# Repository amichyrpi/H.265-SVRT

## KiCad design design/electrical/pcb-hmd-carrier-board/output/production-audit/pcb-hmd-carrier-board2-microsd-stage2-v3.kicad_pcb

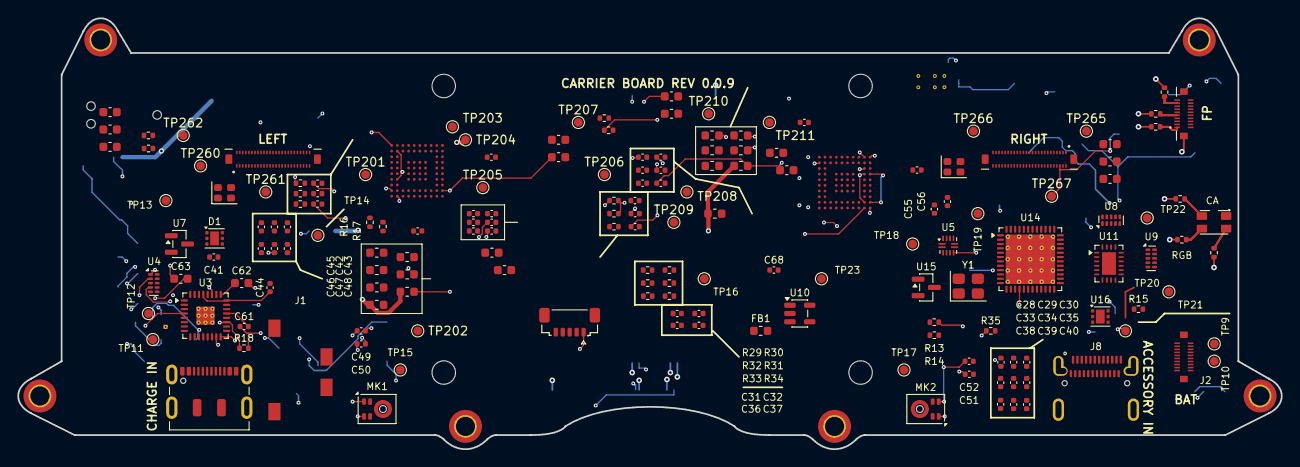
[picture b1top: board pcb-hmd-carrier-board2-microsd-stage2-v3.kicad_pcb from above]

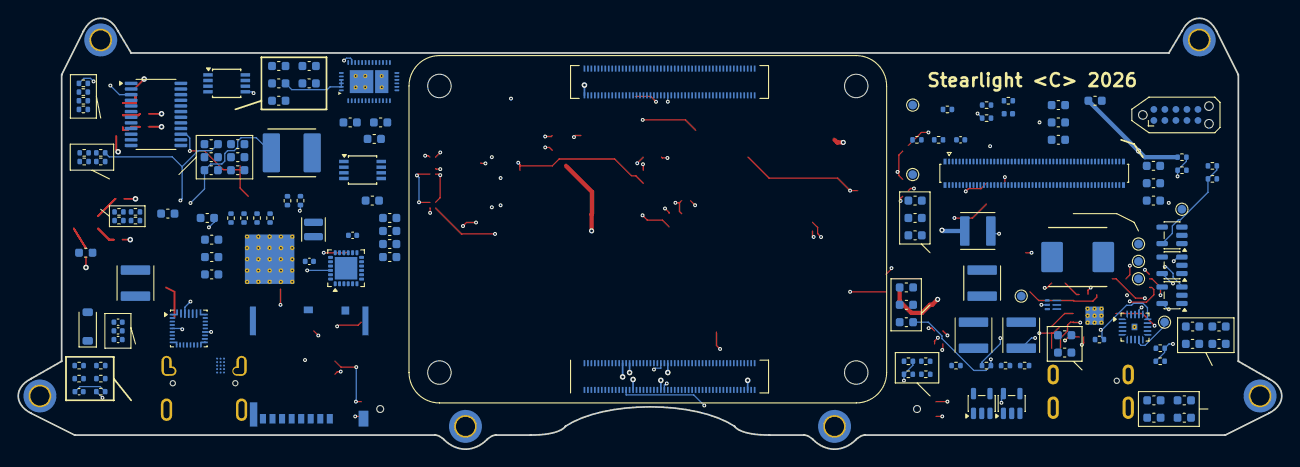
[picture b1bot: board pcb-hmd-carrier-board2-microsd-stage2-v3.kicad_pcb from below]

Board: 6 copper layers, 145.5 x 49.6 mm, 312 parts (138 on the bottom side), 10 nets.

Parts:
C1, C2, C3, C4, C5, C9, C10, C11, C13, C14, C19, C20, C21, C22, C23: 10u; C_0603_1608Metric
C6, C12, C15, C24, C25: 100n; C_0603_1608Metric
C7, C8: 330p; C_0603_1608Metric
C16: 4u7; C_0603_1608Metric
C17, C18: 47n; C_0603_1608Metric
C26, C20120, C20121, C20220, C20221: 1u; C_0603_1608Metric
C27: 47p; C_0603_1608Metric
C28, C29, C30, C31, C32, C33, C34, C35, C36, C37, C43, C48, C290, C291, C2010, C2011, C2012, C2013, C2014, C2015, C2016, C2017, C2020, C2021, C2022, C2023, C2024, C2025, C2026, C2027, C20130, C20131, C20132, C20230, C20231, C20232: 100n; C_0402_1005Metric
C38, C44, C45, C46, C47: 10u; C_0402_1005Metric
C39, C40, C41, C42: 1u; C_0402_1005Metric
C49, C50, C51, C52: 1u C0G; C_0402_1005Metric
C55, C56: 100n PCIe AC; C_0402_1005Metric
C57, C58: 100u low-ESR; C_0603_1608Metric
C59, C60: 22u 25V; C_0603_1608Metric
C61: 100n JACK MIC; C_0402_1005Metric
C62: 47u HP LEFT; C_0603_1608Metric
C63: 47u HP RIGHT; C_0603_1608Metric
C64: 4.7u 10V; C_0603_1608Metric
C65, C66: 10u 6.3V; C_0603_1608Metric
C67: 120p C0G; C_0402_1005Metric
C68: 100n USB3 RESET; C_0402_1005Metric
C260, C265: 2.2uF; C_0603_1608Metric
C261, C262, C266, C267: 1uF 10V; C_0603_1608Metric
C270, C272, C273, C2031, C2041, C2051, C2061: 4.7uF 10V; C_0603_1608Metric
C271: 2.2uF 10V; C_0603_1608Metric
C274: 1uF; C_0603_1608Metric
C280: 68n COMP; C_0402_1005Metric
C281: 10uF 10V; C_0402_1005Metric
C282, C283: 10uF 16V; C_0402_1005Metric
C301: 10uF SD POWER (CM4 LITE ONLY); C_0603_1608Metric
C2032, C2042, C2052, C2062: 10uF 6.3V; C_0603_1608Metric
C20122, C20123, C20222, C20223: 2.2u; C_0603_1608Metric
D1: TVS2200DRVR; WSON-6-1EP_2x2mm_P0.65mm_EP1x1.6mm
D11: TJ-S3227 RGB COMMON ANODE C601674; TOGIALED_TJ-S3227SW1TCGLCCYRGB-A5
D201: DFLS160-7; D_SOD-123
FB1: 600R@100MHz ferrite; L_0603_1608Metric
FB2011, FB2012, FB2013, FB2014, FB2015, FB2016, FB2017, FB2021, FB2022, FB2023, FB2024, FB2025, FB2026, FB2027: 600R@100MHz; L_0603_1608Metric
H1, H2, H3, H4, H5, H6: MountingHole_2.2mm_M2_DIN965_Pad_TopBottom
J1: SJ-43514-SMT-TR; SameSky_SJ-43514-SMT-TR
J2: BM28 BATTERY FLEX 5A + NTC/ID; Hirose_BM28B0.6-20DS_2-0.35V
J6: TAG-CONNECT SERVICE PADS (NO FIT); Tag-Connect_TC2050-IDC-NL_2x05_P1.27mm_Vertical
J7: DF40C-100DP-0.4V(51) TRACKING; Hirose_DF40C-100DP-0.4V_2x50-1MP_P0.4mm
J8: DX07S024JJ2R1300 ACCESSORY; JAE_DX07S024JJ2R1300
J9: DX07S016JA1R1500 CHARGE/SERVICE; USB_C_Receptacle_JAE_DX07S016JA1R1500
J10: PROX SENSOR - SM05B-SURS-TF; JST_SUR_SM05B-SURS-TF_1x05-1MP_P0.80mm_Horizontal
J11: BM28B0.6-20DS/2-0.35V BUTTON FLEX; Hirose_BM28B0.6-20DS_2-0.35V_BUTTONS
J201: J_DISPLAY_LEFT 245863050104829+; Kyocera_245863050104829_50P_P0.35
J202: J_DISPLAY_RIGHT 245863050104829+; Kyocera_245863050104829_50P_P0.35
J301: Molex 503398-1892 (CM4 LITE ONLY); SDCARD_MOLEX_503398-1892
L1: 0.47uH XFL4015-471MEC; L_0402_1005Metric
L2: SRP7050TA-2R2M 2.2uH 10A; Bourns_SRP7050TA
L3: SRP5030CA-1R0M 1uH 9A; Bourns_SRP5030CA
L203, L204, L205, L206: 2.2uH; L_Abracon_ASPI-4030S
L207: 4.7uH 1.6A DFE252010; L_APV_ANR252010
L208: 10uH >=2.5A WLED; L_Abracon_ASPI-4030S
MK1, MK2: IM73A135V01; Infineon_PG-LLGA-5-2
Module1: CM4 2GB/16GB/Wireless; Raspberry-Pi-4-Compute-Module
R1: 220k; R_0402_1005Metric
R2: 30k; R_0402_1005Metric
R3: 5.23k ILIM; R_0402_1005Metric
R4: 137k ILIM; R_0402_1005Metric
R5, R6, R290, R291, R292, R293: 2.2k I2C; R_0402_1005Metric
R7, R8, R294, R295, R2011, R2021: 10k; R_0402_1005Metric
R9: 30.1k TS; R_0402_1005Metric
R10: 10k NTC; R_0402_1005Metric
R11: 100R BATP; R_0402_1005Metric
R12: 6.04k 2S; R_0402_1005Metric
R13, R14: 200k; R_0402_1005Metric
R15: ILIM 1.5A TBD; R_0402_1005Metric
R16, R17: I2C 2.2k; R_0402_1005Metric
R18: MICBIAS 2.7k; R_0402_1005Metric
R19: 75k 1V05 FB; R_0402_1005Metric
R20: 100k 1V05 FB; R_0402_1005Metric
R21: 100k 1V05 PG; R_0402_1005Metric
R22: 10k WIFI EN; R_0402_1005Metric
R23: 10k BT EN; R_0402_1005Metric
R24: 75k MODE; R_0402_1005Metric
R25: 51k MODE; R_0402_1005Metric
R26: 10k CLKREQ; R_0402_1005Metric
R27: 2.2k CHG SCL; R_0402_1005Metric
R28: 2.2k CHG SDA; R_0402_1005Metric
R29: 10k OCI PU; R_0402_1005Metric
R30: 1.6k RREF VERIFY; R_0402_1005Metric
R31: 10k RESET PU; R_0402_1005Metric
R32: 10k SPI CLK PD; R_0402_1005Metric
R33: 10k SPI CS PD; R_0402_1005Metric
R34: 10k SPI MISO PU; R_0402_1005Metric
R35: 10k SPI MOSI PD; R_0402_1005Metric
R73, R76, R77, R78: 1k; R_0402_1005Metric
R74, R75: 330R; R_0402_1005Metric
R260, R265: 100k RESET pulldown; R_0402_1005Metric
R261, R266: 0R DNP to BL_PWM; R_0402_1005Metric
R280: 37.4k 1% ISET=33.2mA; R_0402_1005Metric
R281: 49.9k 1% 1.25MHz; R_0402_1005Metric
R282: 147k 1% OVP; R_0402_1005Metric
R283: 20k 1% OVP; R_0402_1005Metric
R284: 3k COMP; R_0402_1005Metric
R301: 12k 1% SD_PWR_ON PU (CM4 LITE ONLY); R_0402_1005Metric
R302, R303: 0R SD DETECT OPTION; R_0402_1005Metric
R2010, R2020: 2.00k 1%; R_0402_1005Metric
R2012: 10k ADDR 0x0F; R_0402_1005Metric
R2022: 10k ADDR 0x1F; R_0402_1005Metric
R2031: 453k 1%; R_0402_1005Metric
R2032, R2042, R2051, R2052, R2062: 100k 1%; R_0402_1005Metric
R2041: 200k 1%; R_0402_1005Metric
R2061: 91k 1%; R_0402_1005Metric
TP1, TP9, TP10, TP11, TP12, TP13, TP14, TP15, TP16, TP17, TP18, TP19, TP20, TP21, TP22, TP23: CHG_STAT; TestPoint_Pad_D1.0mm
TP2: PGOOD_5V; TestPoint_Pad_D1.0mm
TP3: BAT_ID; TestPoint_Pad_D1.0mm
TP4: +5V_SYS; TestPoint_Pad_D1.0mm
TP5: +3V3; TestPoint_Pad_D1.0mm
TP6: +1V05_USB; TestPoint_Pad_D1.0mm
TP7: GND; TestPoint_Pad_D1.0mm
TP8: VBAT_SYS; TestPoint_Pad_D1.0mm
TP201: DISPLAY_5V; TestPoint_Pad_D1.0mm
TP202: DISPLAY_3V3; TestPoint_Pad_D1.0mm
TP203: DISPLAY_1V8; TestPoint_Pad_D1.0mm
TP204: DISPLAY_1V2; TestPoint_Pad_D1.0mm
TP205: DISPLAY_1V15; TestPoint_Pad_D1.0mm
TP206: LCD_VSP +5V5; TestPoint_Pad_D1.0mm
TP207: LCD_VSN -5V5; TestPoint_Pad_D1.0mm
TP208: BL_EN; TestPoint_Pad_D1.0mm
TP209: BL_PWM GPIO12; TestPoint_Pad_D1.0mm
TP210: I2C_SDA_1V8; TestPoint_Pad_D1.0mm
TP211: I2C_SCL_1V8; TestPoint_Pad_D1.0mm
TP260: L S1_TEST NC; TestPoint_Pad_D1.0mm
TP261: L TE; TestPoint_Pad_D1.0mm
TP262: L LEDPWM; TestPoint_Pad_D1.0mm
TP265: R S1_TEST NC; TestPoint_Pad_D1.0mm
TP266: R TE; TestPoint_Pad_D1.0mm
TP267: R LEDPWM; TestPoint_Pad_D1.0mm
U1: TPS62825DMQR; Texas_DMQ0006A_VSON-HR-6_1.5x1.5mm
U2: TPS568230RJER; Texas_RJE0020A_VQFN-20-1EP_3x3mm_P0.45mm_EP0.675x0.76mm_The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
U3: TLV320AIC3204IRHBR; Texas_RHB0032M_VQFN-32-1EP_5x5mm_P0.5mm_EP2.1x2.1mm_Thermal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
U4: TPD4E05U06DQAR; USON-10_2.5x1.0mm_P0.5mm
U5: TUSB320LAIRWBR; Texas_X2QFN-12_1.6x1.6mm_P0.4mm
U6: BQ25798RQMR; Texas_RQM0029A_VQFN-29_4x4mm_P0.4mm
U7: TPD2EUSB30DRTR; SOT-23
U8, U9: TPD4EUSB30DQAR; USON-10_2.5x1.0mm_P0.5mm
U10: TLV75528PDBVR; SOT-23-5
U11: HD3SS3212IRKSR; Texas_RVC0020A_WQFN-20-1EP_3x4mm_P0.5mm_EP1.6x2.6mm
U12: TPS25751DREFR; Texas_REF0038A_WQFN-38_6x4mm_DualPad
U13: CAT24C512WI-GT3; TSSOP-8_3x3mm_P0.65mm
U14: UPD720202K8-711-BAA-A; QFN-48-1EP_7x7mm_P0.5mm_EP5.7x5.7mm_ThermalVias
U15: TLV803EA30DBZR; SOT-23
U16: TPS2553-1DRVR; WSON-6-1EP_2x2mm_P0.65mm_EP1x1.6mm
U201, U202: TC358870XBG(NOK) C3008712; Toshiba_P-VFBGA80_7x7mm_P0.65
U203, U204, U205, U206: TLV62569DBVR; SOT-23-5
U207: TPS65132B5YFFR; TI_DSBGA15_YFF_2.108x1.514mm_P0.4
U208: MP3387AGRT-P; TQFN-24-1EP_4x4mm_P0.5mm_EP2.6x2.6mm
U209: PCA9306DCTR C123752; TSSOP-8_3x3mm_P0.65mm
U210: TCA9539PWR 1V8 DISPLAY GPIO; TSSOP-24_4.4x7.8mm_P0.65mm
U301: RT9742GGJ5 SD POWER (CM4 LITE ONLY); SOT-23-5
Y1: 24MHz; Crystal_SMD_3225-4Pin_3.2x2.5mm
Y201, Y202: SIT8008ACE73-18E-48.000000E; Oscillator_SMD_SiT_PQFN-4Pin_2.0x1.6mm

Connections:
SD_CLK: J301.5, Module1.57
SD_CMD: J301.3, Module1.62
SD_DAT0: J301.7, Module1.63
SD_DAT1: J301.8, Module1.67
SD_DAT2: J301.1, Module1.69
SD_DAT3: J301.2, Module1.61
SD_DETECT_A: J301.9, R302.1
SD_DETECT_B: J301.10, R303.1, U301.3
SD_PWR: C301.1, J301.4, U301.1
SD_PWR_ON: Module1.75, R301.2, U301.4

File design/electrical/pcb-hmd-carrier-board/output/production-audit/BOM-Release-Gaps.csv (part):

Reference,Value,Missing_release_fields
C1,10u,Manufacturer; MPN; Supplier part number
C10,10u,Manufacturer; MPN; Supplier part number
C11,10u,Manufacturer; MPN; Supplier part number
C12,100n,Manufacturer; MPN; Supplier part number
C13,10u,Manufacturer; MPN; Supplier part number
C14,10u,Manufacturer; MPN; Supplier part number
C15,100n,Manufacturer; MPN; Supplier part number
C16,4u7,Manufacturer; MPN; Supplier part number
C17,47n,Manufacturer; MPN; Supplier part number
C18,47n,Manufacturer; MPN; Supplier part number
C19,10u,Manufacturer; MPN; Supplier part number
C2,10u,Manufacturer; MPN; Supplier part number
C20,10u,Manufacturer; MPN; Supplier part number
C2010,100n,Manufacturer; MPN; Supplier part number
C2011,100n,Manufacturer; MPN; Supplier part number
C2012,100n,Manufacturer; MPN; Supplier part number
C20120,1u,Manufacturer; MPN; Supplier part number
C20121,1u,Manufacturer; MPN; Supplier part number
C20122,2.2u,Manufacturer; MPN; Supplier part number
C20123,2.2u,Manufacturer; MPN; Supplier part number
C2013,100n,Manufacturer; MPN; Supplier part number
C20130,100n,Manufacturer; MPN; Supplier part number
C20131,100n,Manufacturer; MPN; Supplier part number
C20132,100n,Manufacturer; MPN; Supplier part number
C2014,100n,Manufacturer; MPN; Supplier part number
C2015,100n,Manufacturer; MPN; Supplier part number
C2016,100n,Manufacturer; MPN; Supplier part number
C2017,100n,Manufacturer; MPN; Supplier part number
C2020,100n,Manufacturer; MPN; Supplier part number
C2021,100n,Manufacturer; MPN; Supplier part number
C2022,100n,Manufacturer; MPN; Supplier part number
C20220,1u,Manufacturer; MPN; Supplier part number
C20221,1u,Manufacturer; MPN; Supplier part number
C20222,2.2u,Manufacturer; MPN; Supplier part number
C20223,2.2u,Manufacturer; MPN; Supplier part number
C2023,100n,Manufacturer; MPN; Supplier part number
C20230,100n,Manufacturer; MPN; Supplier part number
C20231,100n,Manufacturer; MPN; Supplier part number
C20232,100n,Manufacturer; MPN; Supplier part number
C2024,100n,Manufacturer; MPN; Supplier part number
C2025,100n,Manufacturer; MPN; Supplier part number
C2026,100n,Manufacturer; MPN; Supplier part number
C2027,100n,Manufacturer; MPN; Supplier part number
C2031,4.7uF 10V,Manufacturer; MPN; Supplier part number
C2032,10uF 6.3V,Manufacturer; MPN; Supplier part number
C2041,4.7uF 10V,Manufacturer; MPN; Supplier part number
C2042,10uF 6.3V,Manufacturer; MPN; Supplier part number
C2051,4.7uF 10V,Manufacturer; MPN; Supplier part number
C2052,10uF 6.3V,Manufacturer; MPN; Supplier part number
C2061,4.7uF 10V,Manufacturer; MPN; Supplier part number
C2062,10uF 6.3V,Manufacturer; MPN; Supplier part number
C21,10u,Manufacturer; MPN; Supplier part number
C22,10u,Manufacturer; MPN; Supplier part number
C23,10u,Manufacturer; MPN; Supplier part number
C24,100n,Manufacturer; MPN; Supplier part number
C25,100n,Manufacturer; MPN; Supplier part number
C26,1u,Manufacturer; MPN; Supplier part number
C260,2.2uF,Manufacturer; MPN; Supplier part number
C261,1uF 10V,Manufacturer; MPN; Supplier part number
C262,1uF 10V,Manufacturer; MPN; Supplier part number
C265,2.2uF,Manufacturer; MPN; Supplier part number
C266,1uF 10V,Manufacturer; MPN; Supplier part number
C267,1uF 10V,Manufacturer; MPN; Supplier part number
C27,47p,Manufacturer; MPN; Supplier part number
C270,4.7uF 10V,Manufacturer; MPN; Supplier part number
C271,2.2uF 10V,Manufacturer; MPN; Supplier part number
C272,4.7uF 10V,Manufacturer; MPN; Supplier part number
C273,4.7uF 10V,Manufacturer; MPN; Supplier part number
C274,1uF,Manufacturer; MPN; Supplier part number
C28,100n,Manufacturer; MPN; Supplier part number
C280,68n COMP,Manufacturer; MPN; Supplier part number
C281,10uF 10V,Manufacturer; MPN; Supplier part number
C282,10uF 16V,Manufacturer; MPN; Supplier part number
C283,10uF 16V,Manufacturer; MPN; Supplier part number
C29,100n,Manufacturer; MPN; Supplier part number
C290,100n,Manufacturer; MPN; Supplier part number
C291,100n,Manufacturer; MPN; Supplier part number
C3,10u,Manufacturer; MPN; Supplier part number
C30,100n,Manufacturer; MPN; Supplier part number
C301,10uF SD POWER (CM4 LITE ONLY),Manufacturer; MPN; Supplier part number
C31,100n,Manufacturer; MPN; Supplier part number
C32,100n,Manufacturer; MPN; Supplier part number
C33,100n,Manufacturer; MPN; Supplier part number
C34,100n,Manufacturer; MPN; Supplier part number
C35,100n,Manufacturer; MPN; Supplier part number
C36,100n,Manufacturer; MPN; Supplier part number
C37,100n,Manufacturer; MPN; Supplier part number
C38,10u,Manufacturer; MPN; Supplier part number
C39,1u,Manufacturer; MPN; Supplier part number
C4,10u,Manufacturer; MPN; Supplier part number
C40,1u,Manufacturer; MPN; Supplier part number
C41,1u,Manufacturer; MPN; Supplier part number
C42,1u,Manufacturer; MPN; Supplier part number
C43,100n,Manufacturer; MPN; Supplier part number
C44,10u,Manufacturer; MPN; Supplier part number
C45,10u,Manufacturer; MPN; Supplier part number
C46,10u,Manufacturer; MPN; Supplier part number
C47,10u,Manufacturer; MPN; Supplier part number
C48,100n,Manufacturer; MPN; Supplier part number
C49,1u C0G,Manufacturer; MPN; Supplier part number
C5,10u,Manufacturer; MPN; Supplier part number
C50,1u C0G,Manufacturer; MPN; Supplier part number
C51,1u C0G,Manufacturer; MPN; Supplier part number
C52,1u C0G,Manufacturer; MPN; Supplier part number
C55,100n PCIe AC,Manufacturer; MPN; Supplier part number
C56,100n PCIe AC,Manufacturer; MPN; Supplier part number
C57,100u low-ESR,Manufacturer; MPN; Supplier part number
C58,100u low-ESR,Manufacturer; MPN; Supplier part number
C59,22u 25V,Manufacturer; MPN; Supplier part number
C6,100n,Manufacturer; MPN; Supplier part number
C60,22u 25V,Manufacturer; MPN; Supplier part number
C61,100n JACK MIC,Manufacturer; MPN; Supplier part number
C62,47u HP LEFT,Manufacturer; MPN; Supplier part number
C63,47u HP RIGHT,Manufacturer; MPN; Supplier part number
C64,4.7u 10V,Manufacturer; MPN; Supplier part number
C65,10u 6.3V,Manufacturer; MPN; Supplier part number
C66,10u 6.3V,Manufacturer; MPN; Supplier part number
C67,120p C0G,Manufacturer; MPN; Supplier part number
C68,100n USB3 RESET,Manufacturer; MPN; Supplier part number
C7,330p,Manufacturer; MPN; Supplier part number
C8,330p,Manufacturer; MPN; Supplier part number
C9,10u,Manufacturer; MPN; Supplier part number
D1,TVS2200DRVR,Manufacturer; MPN; Supplier part number
D11,TJ-S3227 RGB COMMON ANODE C601674,Manufacturer; MPN; Supplier part number
D201,DFLS160-7,Manufacturer; MPN; Supplier part number
FB1,600R@100MHz ferrite,Manufacturer; MPN; Supplier part number
FB2011,600R@100MHz,Manufacturer; MPN; Supplier part number
FB2012,600R@100MHz,Manufacturer; MPN; Supplier part number
FB2013,600R@100MHz,Manufacturer; MPN; Supplier part number
FB2014,600R@100MHz,Manufacturer; MPN; Supplier part number
FB2015,600R@100MHz,Manufacturer; MPN; Supplier part number
FB2016,600R@100MHz,Manufacturer; MPN; Supplier part number
FB2017,600R@100MHz,Manufacturer; MPN; Supplier part number
FB2021,600R@100MHz,Manufacturer; MPN; Supplier part number
FB2022,600R@100MHz,Manufacturer; MPN; Supplier part number
FB2023,600R@100MHz,Manufacturer; MPN; Supplier part number
FB2024,600R@100MHz,Manufacturer; MPN; Supplier part number
FB2025,600R@100MHz,Manufacturer; MPN; Supplier part number
FB2026,600R@100MHz,Manufacturer; MPN; Supplier part number
FB2027,600R@100MHz,Manufacturer; MPN; Supplier part number
J1,SJ-43514-SMT-TR,Manufacturer; MPN; Supplier part number
J10,PROX SENSOR - SM05B-SURS-TF,Manufacturer; MPN; Supplier part number
J11,BM28B0.6-20DS/2-0.35V BUTTON FLEX,Manufacturer; MPN; Supplier part number
J2,BM28 BATTERY FLEX 5A + NTC/ID,Manufacturer; MPN; Supplier part number
J201,J_DISPLAY_LEFT 245863050104829+,Manufacturer; MPN; Supplier part number
J202,J_DISPLAY_RIGHT 245863050104829+,Manufacturer; MPN; Supplier part number
J301,Molex 503398-1892 (CM4 LITE ONLY),Manufacturer; MPN; Supplier part number
J7,DF40C-100DP-0.4V(51) TRACKING,Manufacturer; MPN; Supplier part number
J8,DX07S024JJ2R1300 ACCESSORY,Manufacturer; MPN
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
